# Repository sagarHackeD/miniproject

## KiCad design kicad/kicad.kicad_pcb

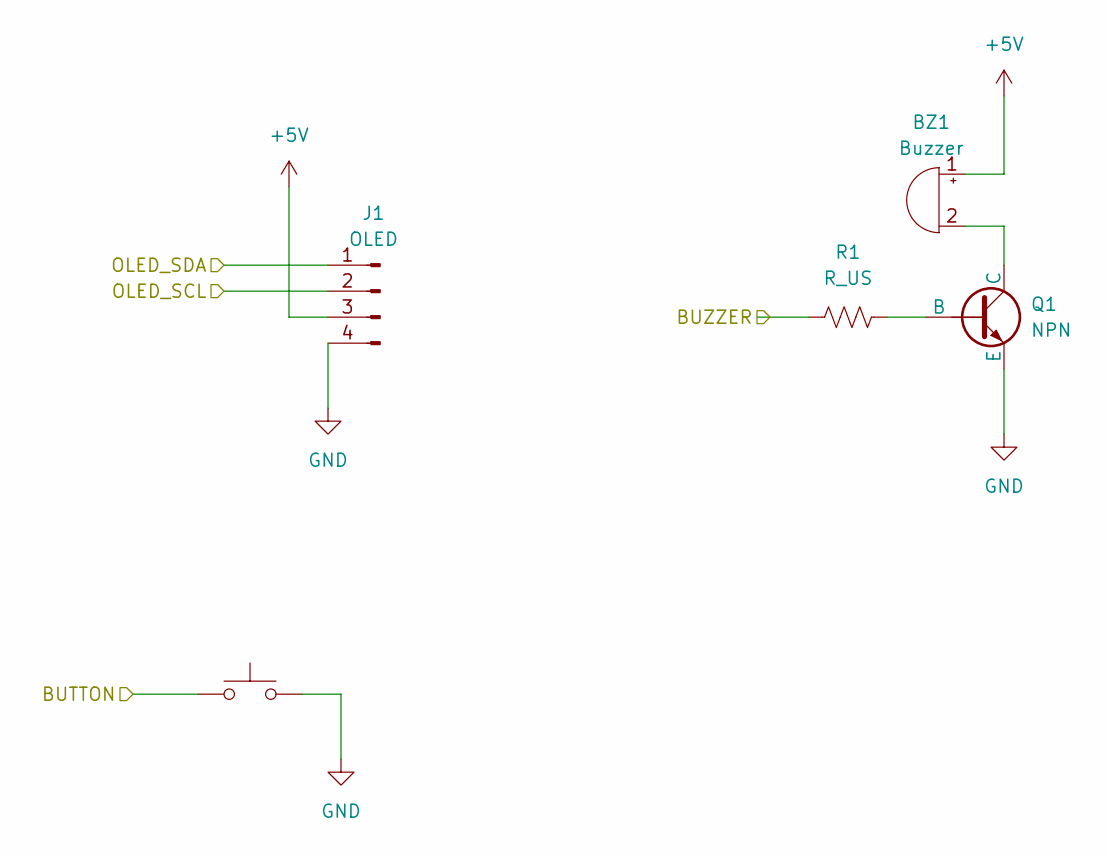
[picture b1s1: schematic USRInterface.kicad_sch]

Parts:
BZ1: Buzzer; Buzzer_12x9.5RM7.6
J1: OLED; PinSocket_1x04_P2.54mm_Vertical
Q1: NPN; TO-92L_Inline_Wide
R1: R_US; R_Axial_DIN0204_L3.6mm_D1.6mm_P7.62mm_Horizontal
SW3: SW_Push; SW_Push_1P1T_XKB_TS-1187A

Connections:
+5V: BZ1.1 (+), J1.3; also elsewhere on the board
/Microcontroller/BUTTON: SW3.1; also elsewhere on the board
/Microcontroller/BUZZER: R1.1; also elsewhere on the board
/Microcontroller/OLED_SCL: J1.2; also elsewhere on the board
/Microcontroller/OLED_SDA: J1.1; also elsewhere on the board
GND: J1.4, Q1.3 (E), SW3.2; also elsewhere on the board
unnamed: BZ1.2 (-), Q1.1 (C)
unnamed: Q1.2 (B), R1.2

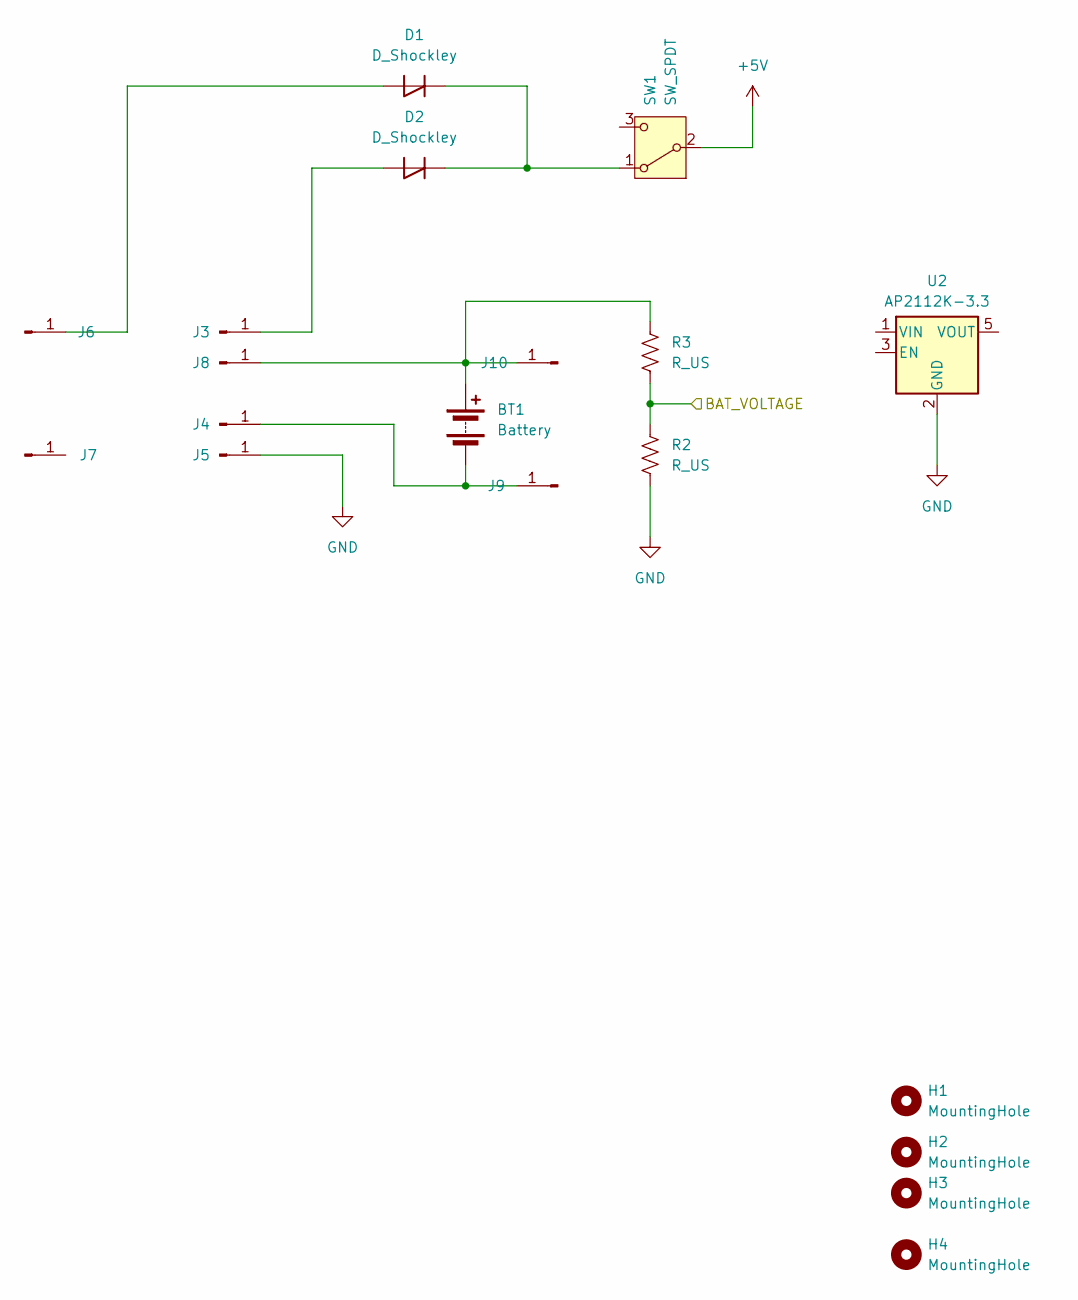
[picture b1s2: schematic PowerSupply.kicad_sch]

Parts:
BT1: Battery; BatteryHolder_Keystone_1042_1x18650
D1, D2: D_Shockley; D_SOD-123F
H1, H2, H3, H4: MountingHole; MountingHole_2.2mm_M2
J3, J4, J5, J6, J7, J8: Conn_01x01_Pin; PinHeader_1x01_P2.54mm_Vertical
J9, J10: Conn_01x01_Pin; SolderWirePad_1x01_SMD_3x6mm
R2, R3: R_US; R_Axial_DIN0204_L3.6mm_D1.6mm_P7.62mm_Horizontal
SW1: SW_SPDT; SW_Slide_SPDT_Angled_CK_OS102011MA1Q
U2: AP2112K-3.3; SOT-23-5

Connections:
+5V: SW1.2 (B); also elsewhere on the board
/Microcontroller/BAT_VOLTAGE: R2.1, R3.2; also elsewhere on the board
GND: J5.1 (Pin_1_1), R2.2, U2.2 (GND_2); also elsewhere on the board
unnamed: BT1.1 (+), J8.1 (Pin_1_1), J10.1 (Pin_1_1), R3.1
unnamed: BT1.2 (-), J4.1 (Pin_1_1), J9.1 (Pin_1_1)
unnamed: D1.2 (A), J6.1 (Pin_1_1)
unnamed: D1.1 (K), D2.1 (K), SW1.1 (A)
unnamed: D2.2 (A), J3.1 (Pin_1_1)

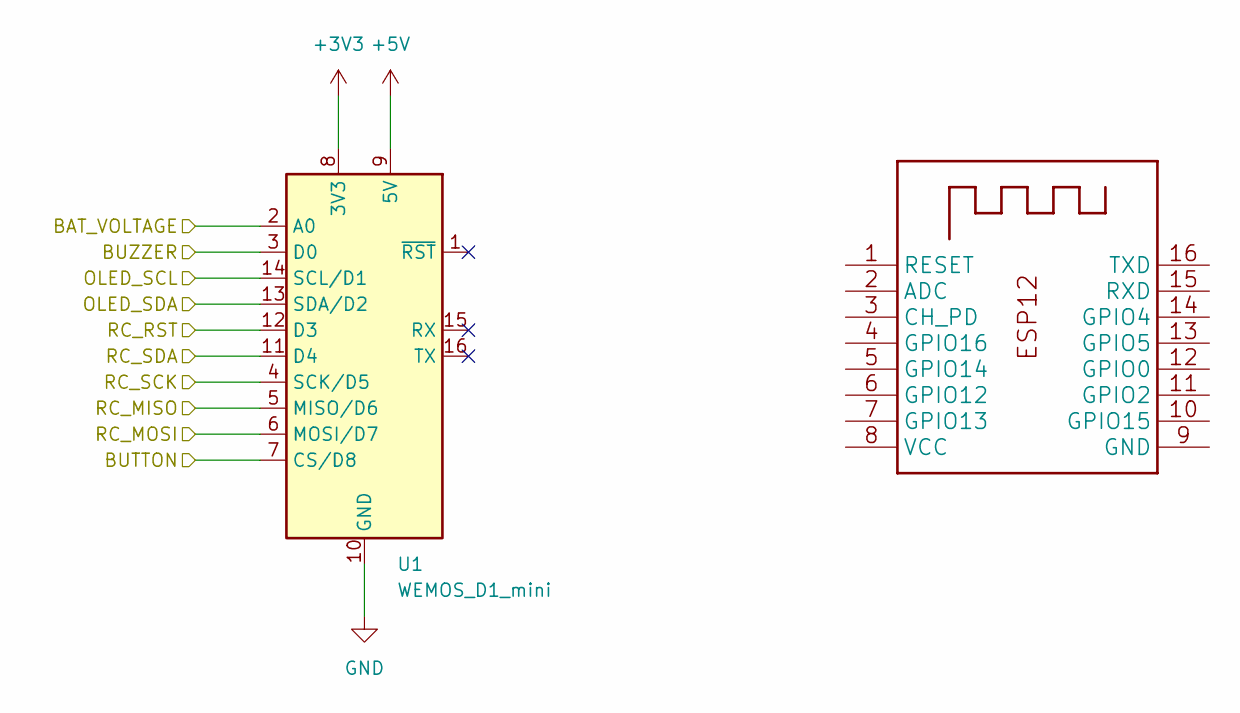
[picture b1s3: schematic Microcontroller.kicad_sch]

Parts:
U1: WEMOS_D1_mini; WEMOS_D1_mini_light
X1: ESP-12

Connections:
+3V3: U1.8 (3V3); also elsewhere on the board
+5V: U1.9 (5V); also elsewhere on the board
/Microcontroller/BAT_VOLTAGE: U1.2 (A0); also elsewhere on the board
/Microcontroller/BUTTON: U1.7 (CS/D8); also elsewhere on the board
/Microcontroller/BUZZER: U1.3 (D0); also elsewhere on the board
/Microcontroller/OLED_SCL: U1.14 (SCL/D1); also elsewhere on the board
/Microcontroller/OLED_SDA: U1.13 (SDA/D2); also elsewhere on the board
/Microcontroller/RC_MISO: U1.5 (MISO/D6); also elsewhere on the board
/Microcontroller/RC_MOSI: U1.6 (MOSI/D7); also elsewhere on the board
/Microcontroller/RC_RST: U1.12 (D3); also elsewhere on the board
/Microcontroller/RC_SCK: U1.4 (SCK/D5); also elsewhere on the board
/Microcontroller/RC_SDA: U1.11 (D4); also elsewhere on the board
GND: U1.10 (GND); also elsewhere on the board

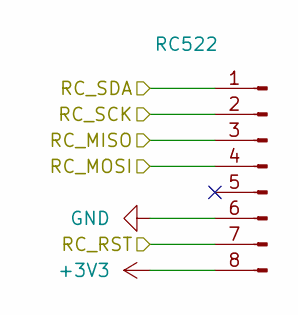
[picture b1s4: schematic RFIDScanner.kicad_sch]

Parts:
J2: RC522; PinSocket_1x08_P2.54mm_Vertical

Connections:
+3V3: J2.8; also elsewhere on the board
/Microcontroller/RC_MISO: J2.3; also elsewhere on the board
/Microcontroller/RC_MOSI: J2.4; also elsewhere on the board
/Microcontroller/RC_RST: J2.7; also elsewhere on the board
/Microcontroller/RC_SCK: J2.2; also elsewhere on the board
/Microcontroller/RC_SDA: J2.1; also elsewhere on the board
GND: J2.6; also elsewhere on the board

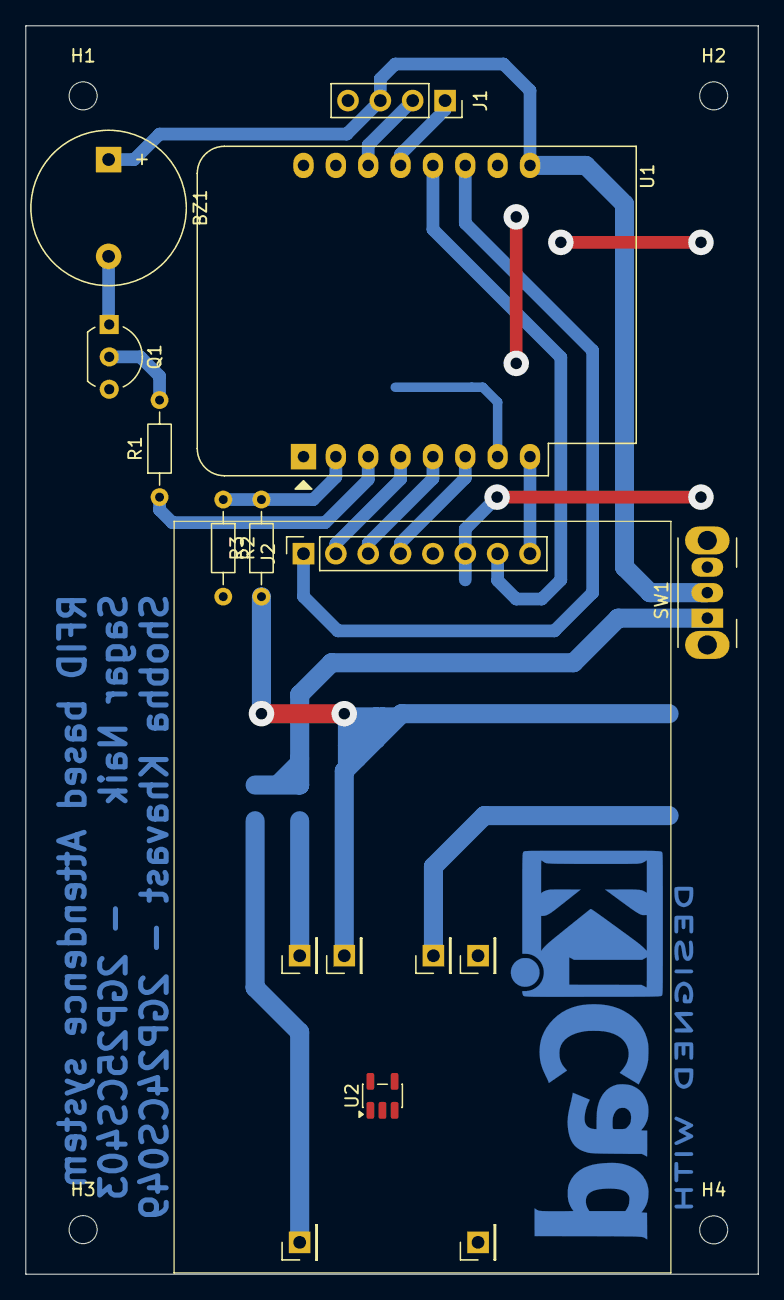
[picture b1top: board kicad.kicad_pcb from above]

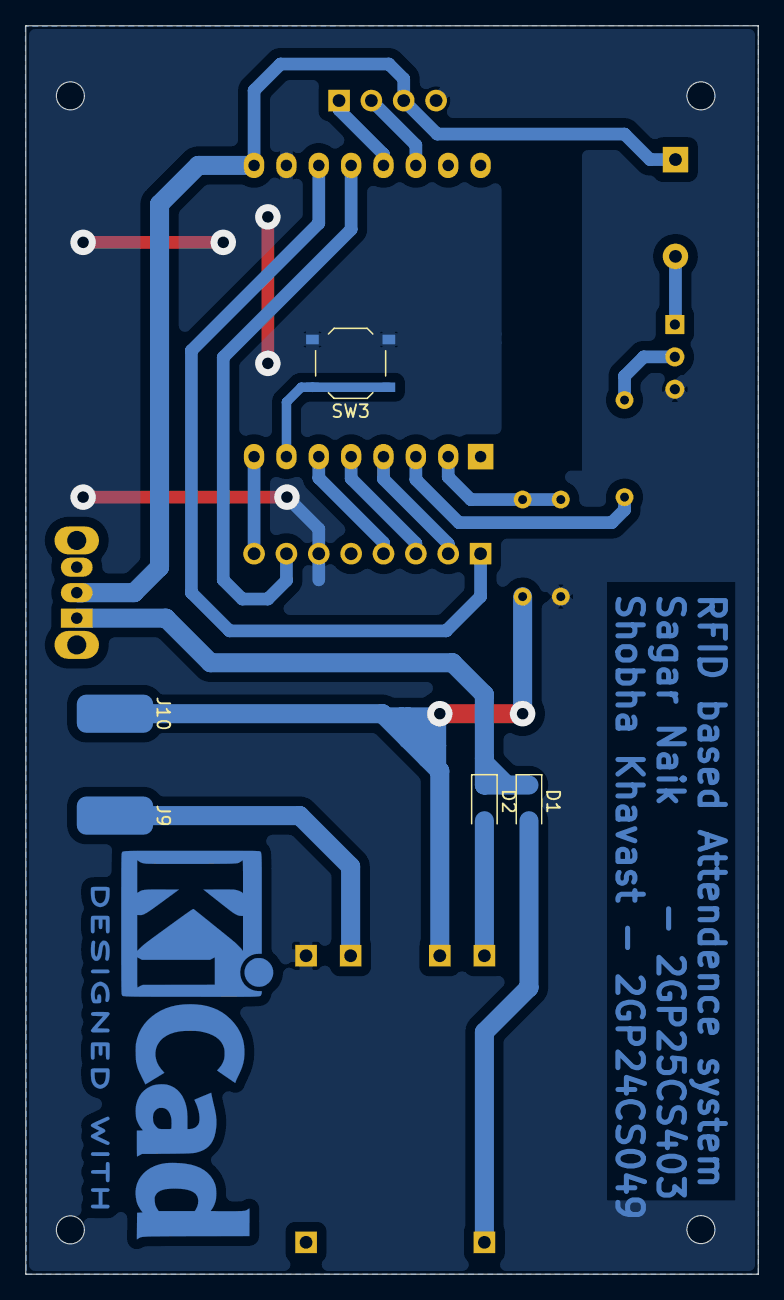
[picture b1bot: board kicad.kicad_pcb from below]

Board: 2 copper layers, 57.5 x 98.0 mm, 25 parts (5 on the bottom side), 20 nets.

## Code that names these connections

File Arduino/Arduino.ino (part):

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// NodeMCU / ESP-12E pin labels
constexpr uint8_t RFID_SS_PIN = D4;
constexpr uint8_t RFID_RST_PIN = D3;
constexpr uint8_t BUZZER_PIN = D0;
constexpr uint8_t OLED_SDA_PIN = D2;
constexpr uint8_t OLED_SCL_PIN = D1;
constexpr uint8_t OLED_ADDRESS = 0x3C; // Change to 0x3D if required by your display.
// Connect battery+ -> 4.7 kOhm -> A0 -> 1 kOhm -> GND.
constexpr float BATTERY_DIVIDER_TOP_RESISTOR_OHMS = 4700.0F;
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}

void beep(uint16_t durationMs = 100) {
  digitalWrite(BUZZER_PIN, HIGH);
  delay(durationMs);
  digitalWrite(BUZZER_PIN, LOW);
}

void playGreetingSound() {
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
void setup() {
  Serial.begin(115200);
  pinMode(BUZZER_PIN, OUTPUT);
  digitalWrite(BUZZER_PIN, LOW);
  WiFi.persistent(false);
  WiFi.setAutoReconnect(true);

  Wire.begin(OLED_SDA_PIN, OLED_SCL_PIN);
  if (!display.begin(SSD1306_SWITCHCAPVCC, OLED_ADDRESS)) {
    Serial.println(F("SSD1306 initialization failed."));
    while (true) {
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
